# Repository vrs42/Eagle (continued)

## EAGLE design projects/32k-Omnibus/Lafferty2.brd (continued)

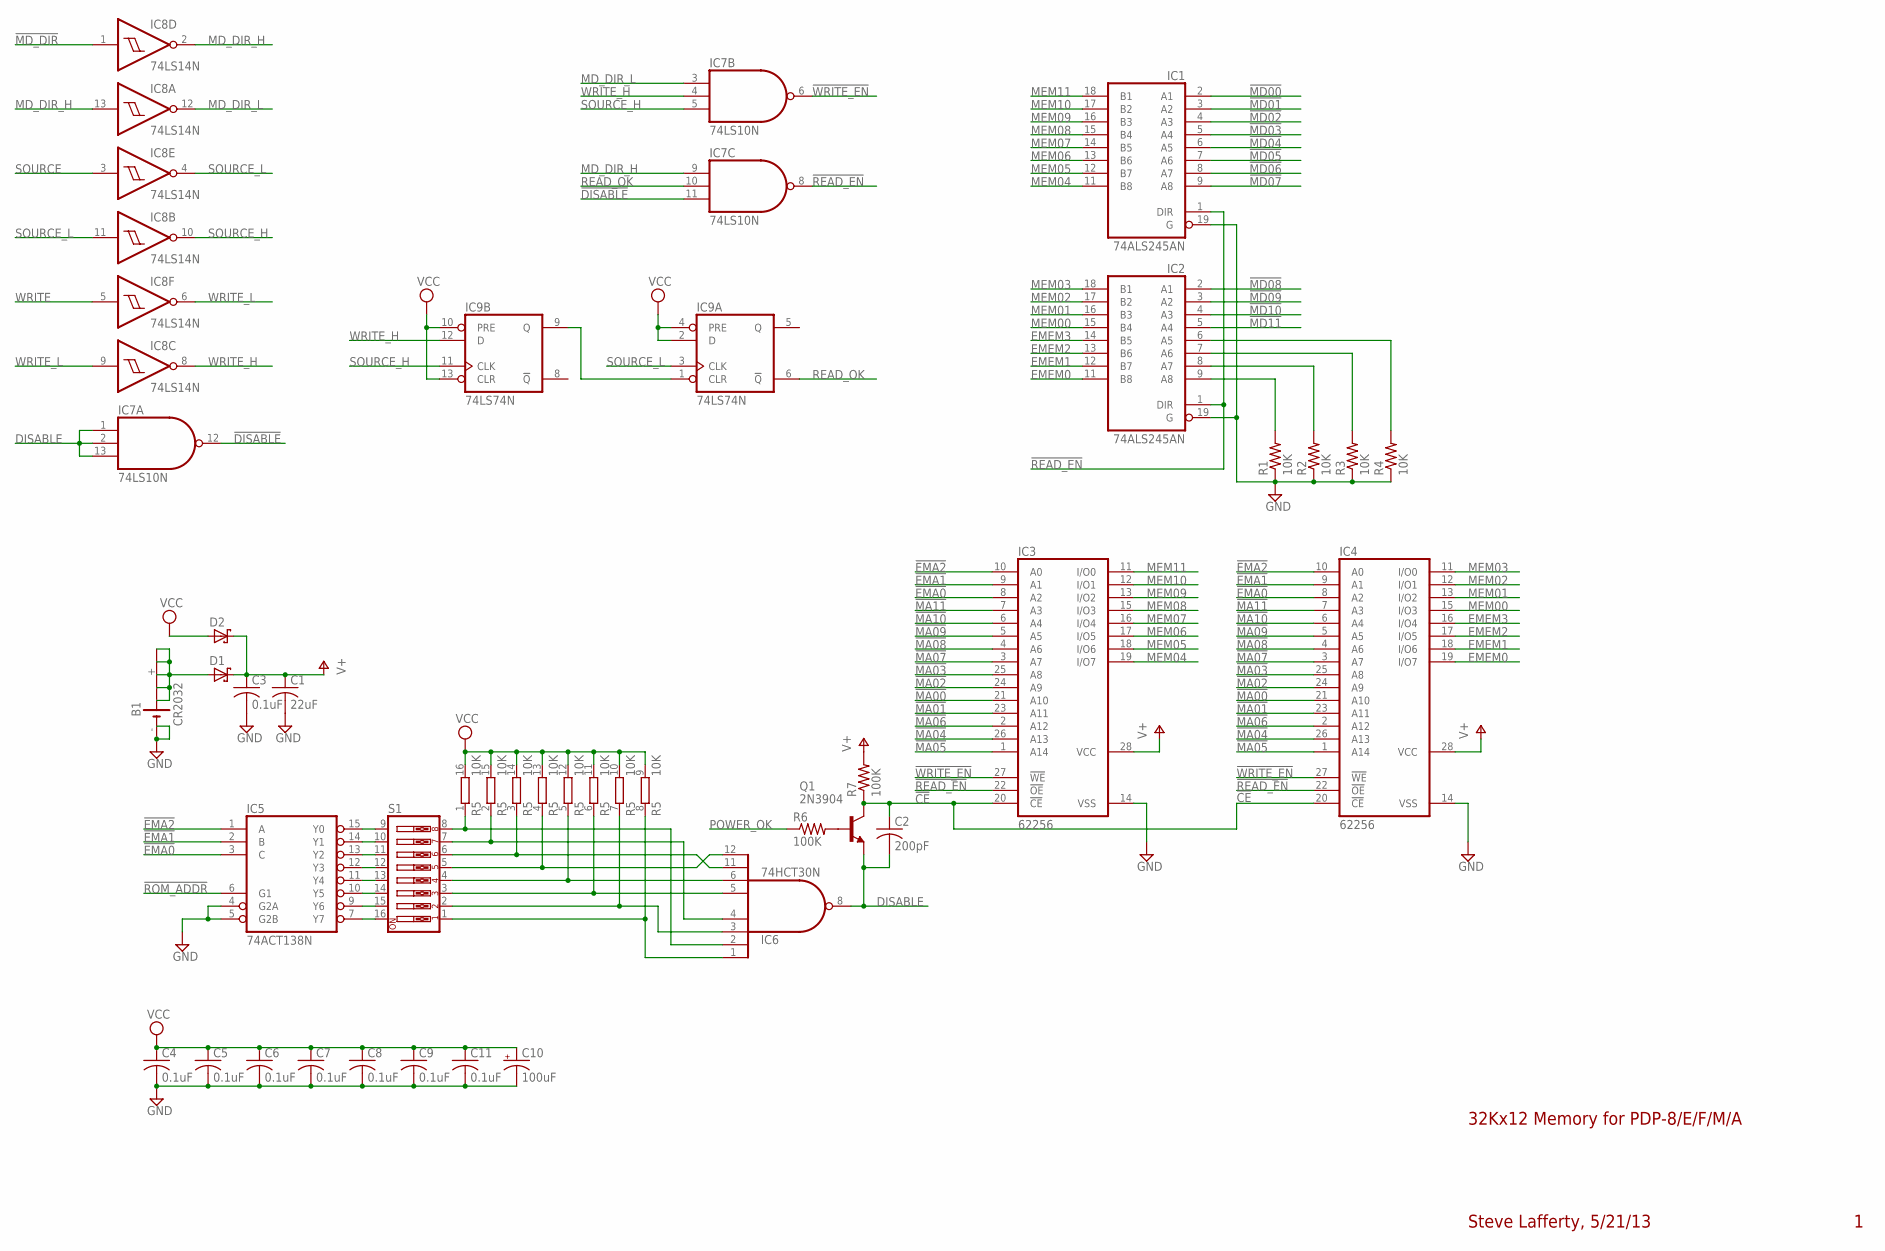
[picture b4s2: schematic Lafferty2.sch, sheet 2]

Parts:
B1: CR2032; B2430UNI
C1: 22uF; C050-025X075
C2: 200pF; C050-025X075
C3, C4, C5, C6, C7, C8, C9, C11: 0.1uF; C050-025X075
C10: 100uF; E12-8
D1, D2: BAT19; DO35-10
IC1, IC2: 74ALS245AN; DIL20
IC3, IC4: 62256; DIL28-6
IC5: 74ACT138N; DIL16
IC6: 74HCT30N; DIL14
IC7: 74LS10N; DIL14
IC8: 74LS14N; DIL14
IC9: 74LS74N; DIL14
Q1: 2N3904; TO92
R1, R2, R3, R4: 10K; 0207/10
R5: 10K; DIL16
R6, R7: 100K; 0207/10
S1: SW_DIP-8; EDG-08

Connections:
!CE: C2.1, IC3.20 (!CE), IC4.20 (!CE), Q1.1 (C), R7.1
!DISABLE: IC7.11 (I2), IC7.12 (O)
!EMA0: IC3.8 (A2), IC4.8 (A2), IC5.3 (C); also elsewhere on the board
!EMA1: IC3.9 (A1), IC4.9 (A1), IC5.2 (B); also elsewhere on the board
!EMA2: IC3.10 (A0), IC4.10 (A0), IC5.1 (A); also elsewhere on the board
!MA00: IC3.21 (A10), IC4.21 (A10); also elsewhere on the board
!MA01: IC3.23 (A11), IC4.23 (A11); also elsewhere on the board
!MA02: IC3.24 (A9), IC4.24 (A9); also elsewhere on the board
!MA03: IC3.25 (A8), IC4.25 (A8); also elsewhere on the board
!MA04: IC3.26 (A13), IC4.26 (A13); also elsewhere on the board
!MA05: IC3.1 (A14), IC4.1 (A14); also elsewhere on the board
!MA06: IC3.2 (A12), IC4.2 (A12); also elsewhere on the board
!MA07: IC3.3 (A7), IC4.3 (A7); also elsewhere on the board
!MA08: IC3.4 (A6), IC4.4 (A6); also elsewhere on the board
!MA09: IC3.5 (A5), IC4.5 (A5); also elsewhere on the board
!MA10: IC3.6 (A4), IC4.6 (A4); also elsewhere on the board
!MA11: IC3.7 (A3), IC4.7 (A3); also elsewhere on the board
!MD00: IC1.2 (A1); also elsewhere on the board
!MD01: IC1.3 (A2); also elsewhere on the board
!MD02: IC1.4 (A3); also elsewhere on the board
!MD03: IC1.5 (A4); also elsewhere on the board
!MD04: IC1.6 (A5); also elsewhere on the board
!MD05: IC1.7 (A6); also elsewhere on the board
!MD06: IC1.8 (A7); also elsewhere on the board
!MD07: IC1.9 (A8); also elsewhere on the board
!MD08: IC2.2 (A1); also elsewhere on the board
!MD09: IC2.3 (A2); also elsewhere on the board
!MD10: IC2.4 (A3); also elsewhere on the board
!MD11: IC2.5 (A4); also elsewhere on the board
!MD_DIR: IC8.1 (I); also elsewhere on the board
!READ_EN: IC1.1 (DIR), IC2.1 (DIR), IC3.22 (!OE), IC4.22 (!OE), IC7.8 (O)
!ROM_ADDR: IC5.6 (G1); also elsewhere on the board
!WRITE_EN: IC3.27 (!WE), IC4.27 (!WE), IC7.6 (O)
DISABLE: C2.2, IC6.8 (O), IC7.1 (I0), IC7.2 (I1), IC7.13 (I2), Q1.3 (E)
EMEM0: IC2.11 (B8), IC4.19 (I/O7)
EMEM1: IC2.12 (B7), IC4.18 (I/O6)
EMEM2: IC2.13 (B6), IC4.17 (I/O5)
EMEM3: IC2.14 (B5), IC4.16 (I/O4)
GND: B1.-, B1.-@1 (-), C1.2, C3.2, C4.2, C5.2, C6.2, C7.2, C8.2, C9.2, C10.-, C11.2, IC1.10 (GND), IC1.19 (G), IC2.10 (GND), IC2.19 (G), IC3.14 (VSS), IC4.14 (VSS), IC5.4 (G2A), IC5.5 (G2B), IC5.8 (GND), IC6.7 (GND), IC7.7 (GND), IC8.7 (GND), IC9.7 (GND), R1.1, R2.1, R3.1, R4.1; also elsewhere on the board
MD_DIR_H: IC7.9 (I0), IC8.2 (O), IC8.13 (I)
MD_DIR_L: IC7.3 (I0), IC8.12 (O)
MEM00: IC2.15 (B4), IC4.15 (I/O3)
MEM01: IC2.16 (B3), IC4.13 (I/O2)
MEM02: IC2.17 (B2), IC4.12 (I/O1)
MEM03: IC2.18 (B1), IC4.11 (I/O0)
MEM04: IC1.11 (B8), IC3.19 (I/O7)
MEM05: IC1.12 (B7), IC3.18 (I/O6)
MEM06: IC1.13 (B6), IC3.17 (I/O5)
MEM07: IC1.14 (B5), IC3.16 (I/O4)
MEM08: IC1.15 (B4), IC3.15 (I/O3)
MEM09: IC1.16 (B3), IC3.13 (I/O2)
MEM10: IC1.17 (B2), IC3.12 (I/O1)
MEM11: IC1.18 (B1), IC3.11 (I/O0)
unnamed: IC5.7 (Y7), S1.16
unnamed: IC5.9 (Y6), S1.15
unnamed: IC5.10 (Y5), S1.14
unnamed: IC5.11 (Y4), S1.13
unnamed: IC5.12 (Y3), S1.12
unnamed: IC5.13 (Y2), S1.11
unnamed: IC5.14 (Y1), S1.10
unnamed: IC5.15 (Y0), S1.9
unnamed: B1.+, B1.+@1 (+), B1.+@2 (+), B1.+@3 (+), B1.+@4 (+), D1.A
unnamed: IC6.12 (I7), R5.4 (1), S1.5
unnamed: IC6.11 (I6), R5.3 (1), S1.6
unnamed: IC6.6 (I5), R5.5 (1), S1.4
unnamed: IC6.5 (I4), R5.6 (1), S1.3
unnamed: IC6.3 (I2), R5.7 (1), S1.2
unnamed: IC6.1 (I0), R5.8 (1), S1.1
unnamed: IC6.2 (I1), R5.1, S1.8
unnamed: IC6.4 (I3), R5.2 (1), S1.7
unnamed: IC2.6 (A5), R4.2
unnamed: Q1.2 (B), R6.2
unnamed: IC2.7 (A6), R3.2
unnamed: IC2.8 (A7), R2.2
unnamed: IC2.9 (A8), R1.2
unnamed: IC9.1 (CLR), IC9.9 (Q)
POWER_OK: R6.1; also elsewhere on the board
READ_OK: IC7.10 (I1), IC9.6 (!Q)
SOURCE: IC8.3 (I); also elsewhere on the board
SOURCE_H: IC7.5 (I2), IC8.10 (O), IC9.11 (CLK)
SOURCE_L: IC8.4 (O), IC8.11 (I), IC9.3 (CLK)
V+: C1.1, C3.1, D1.C, D2.C, IC3.28 (VCC), IC4.28 (VCC), R7.2
VCC: C4.1, C5.1, C6.1, C7.1, C8.1, C9.1, C10.+, C11.1, D2.A, IC1.20 (VCC), IC2.20 (VCC), IC5.16 (VCC), IC6.14 (VCC), IC7.14 (VCC), IC8.14 (VCC), IC9.2 (D), IC9.4 (PRE), IC9.10 (PRE), IC9.13 (CLR), IC9.14 (VCC), R5.9 (2), R5.10 (2), R5.11 (2), R5.12 (2), R5.13 (2), R5.14 (2), R5.15 (2), R5.16 (2); also elsewhere on the board
WRITE: IC8.5 (I); also elsewhere on the board
WRITE_H: IC7.4 (I1), IC8.8 (O), IC9.12 (D)
WRITE_L: IC8.6 (O), IC8.9 (I)

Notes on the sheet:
32Kx12 Memory for PDP-8/E/F/M/A
Steve Lafferty, 5/21/13

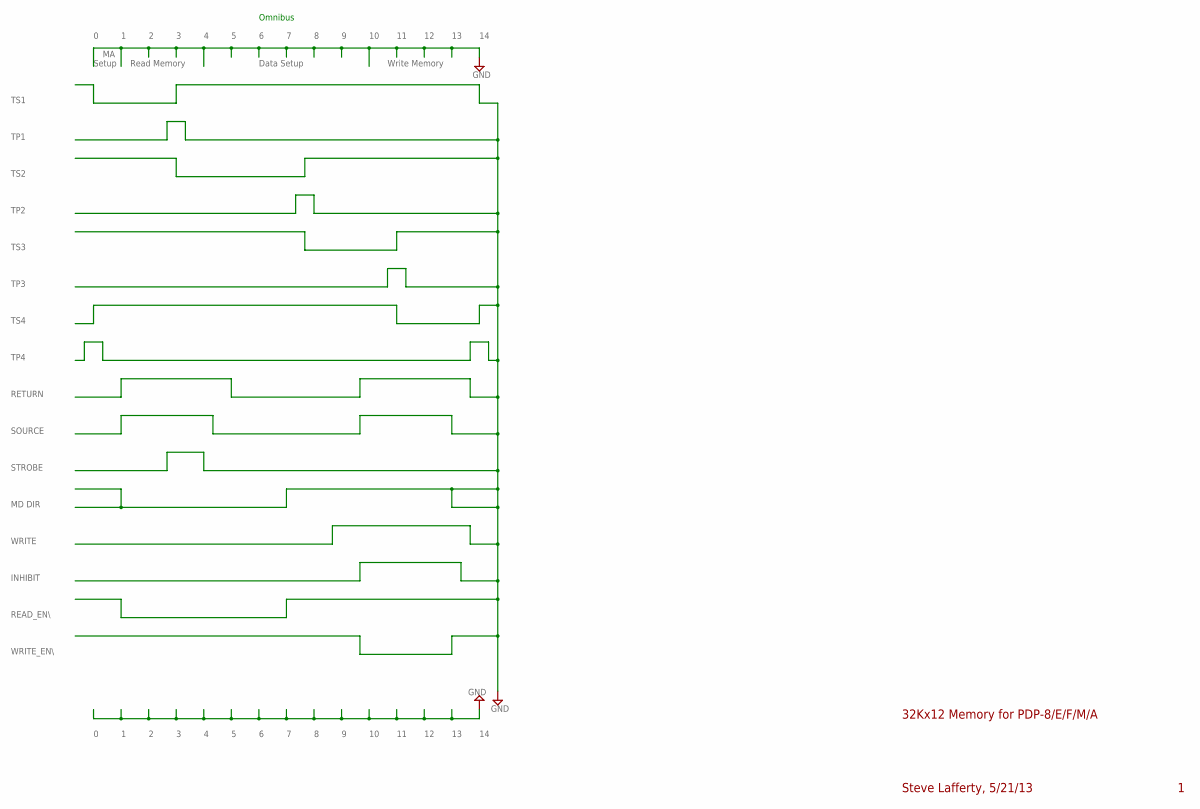
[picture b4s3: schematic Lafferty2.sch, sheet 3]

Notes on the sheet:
TS1
TS2
TS3
TS4
TP1
TP2
TP3
TP4
INHIBIT
WRITE
STROBE
SOURCE
RETURN
MD DIR
Setup
Read Memory
Data Setup
Write Memory
Omnibus
READ_EN\\
WRITE_EN\\
32Kx12 Memory for PDP-8/E/F/M/A
Steve Lafferty, 5/21/13
